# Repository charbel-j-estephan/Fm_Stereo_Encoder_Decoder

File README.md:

# FM Stereo Encoder and Decoder

An FM stereo transmission system that stays compatible with mono receivers. The encoder turns a left (G) and right (D) audio signal into one stereo multiplex (MPX) signal that drives an FM modulator. The decoder takes the received MPX and rebuilds G and D.

Communication Systems project, Notre Dame University Louaize.

## How it works

The encoder sends three things at once.

| Part                                 | Frequency       | Purpose                                       |
| ------------------------------------ | --------------- | --------------------------------------------- |
| G + D                                | 30 Hz to 15 kHz | What a mono receiver plays                    |
| 19 kHz pilot                         | 19 kHz          | Tells a stereo receiver to decode             |
| G − D on a suppressed 38 kHz carrier | 23 to 53 kHz    | The extra information a stereo receiver needs |

A mono receiver keeps only the band below 15 kHz, so it plays G + D. A stereo receiver locks to the pilot, doubles it to 38 kHz, recovers G − D and then rebuilds G and D.

## Repository layout

```
Encoder/              KiCad project and exports for the encoder board
Decoder/              KiCad project and exports for the decoder board
Simulation/LTspice/   LTspice encoder and decoder circuits with their models
Simulation/Simulink/  Simulink model of the full stereo FM system
Report/               IEEE format project report (encoder)
docs/img/             Images used in this README
  report/             Figures taken from the project report
  schematic/          Section views of the encoder schematic
```

### Encoder

| File                                            | What it is                         |
| ----------------------------------------------- | ---------------------------------- |
| `Encoder.kicad_pro`, `.kicad_sch`, `.kicad_pcb` | KiCad 10 project                   |
| `MC1496.kicad_sym`, `R0.kicad_sym`              | Symbol libraries the project needs |
| `Encoder_Schematic_color.pdf`                   | Full schematic in colour, A2 sheet |
| `Encoder_PCB_top_1to1_color.pdf`                | Top side of the board at 1:1 scale |
| `Encoder_3D_top.png`                            | 3D render of the board             |
| `FM_Encoder_Buy_List.xlsx`                      | Parts list with prices             |

Signal chain:

1. Input protection and AC coupling on both channels
2. TL072 buffers and Sallen Key low pass filters at 15 kHz
3. Sum (G + D) and difference (G − D) op amp matrix
4. CD4046 phase locked loop with a CD4013 divider, locked to an external 19 kHz reference, gives a 38 kHz carrier
5. MC1496 balanced modulator puts G − D on the 38 kHz carrier
6. MPX summer adds G + D, the modulated G − D and the pilot
7. NE5532 output low pass filters, then out on J4

#### Encoder schematic

The whole encoder fits on one A2 sheet. Each stage sits in its own framed section with a title and a one line note, and every stage output has a named test point.

Audio input and 15 kHz low pass filters. AC coupling, diode clamps to the ±9 V rails and a unity gain buffer on each channel, then two Sallen Key stages.

Sum and difference matrix. U6 makes G + D and U5 makes G − D.

38 kHz balanced modulator. The MC1496 puts G − D on the 38 kHz carrier, and U10A turns its differential output into one signal.

MPX summer and output filter. U8B adds G + D, the DSB signal and the 19 kHz pilot, U8A inverts it back, and three Sallen Key stages drive J4.

PLL. The CD4046 VCO runs at 38 kHz, and the CD4013 divides it by 2 so it locks to the 19 kHz pilot. JP1 picks the VCO or its inverted copy, then R54 and R55 set the carrier level.

Power input and decoupling. Reverse protection diodes, 22 µF bulk caps and a 100 nF pair on every op amp.

Test points, one header pin per stage output plus the ground pins.

Board facts:

- Runs from ±9 V on J1 and J2
- Audio in on J3 (pin 1 left, pin 2 right, pin 4 ground)
- 19 kHz reference in on J5
- MPX out on J4 (pin 1 signal, pin 4 ground)
- JP1 flips the carrier phase if left and right come out swapped
- About 149 by 150 mm, hand soldered, every IC in a socket, header pins as test points

| PCB layout                                                  | 3D view                                                            |
| ----------------------------------------------------------- | ------------------------------------------------------------------ |
|  |  |

| Fabricated PCB before assembly                                | Assembled board                                                       |
| ------------------------------------------------------------- | --------------------------------------------------------------------- |
|  |  |

### Decoder

| File                                            | What it is                         |
| ----------------------------------------------- | ---------------------------------- |
| `Decoder.kicad_pro`, `.kicad_sch`, `.kicad_pcb` | KiCad 10 project                   |
| `Decoder_Schematic_color.pdf`                   | Full schematic in colour           |
| `Decoder_PCB_top_1to1_color.pdf`                | Top side of the board at 1:1 scale |
| `Decoder_3D_top.png`                            | 3D render of the board             |

Signal chain:

1. NE5532 MPX input buffer
2. 15 kHz low pass cascade to recover G + D, which also feeds the mono output
3. CD4046 phase locked loop with a CD4013 divider regenerates the 38 kHz carrier from the 19 kHz reference
4. MC1496 demodulates G − D, followed by a second 15 kHz low pass cascade
5. RV1 and RV2 trim the levels, then a TL072 matrix forms G and D
6. A CD4052 switch selects stereo or mono, and TL072 stages drive the outputs

## Simulation

### LTspice

| File | What it is |
| --- | --- |
| `FM_Encoder.asc` | Full encoder circuit, 20 ms transient run |
| `FM_Decoder.asc` | Decoder circuit, fed by the recorded encoder output |
| `FM_Encoder_schematic.pdf` | Printed encoder schematic |
| `tl072.cir`, `NE5532.sub`, `mc1496.lib`, `CD4046.sub`, `CD4013.sub` | Part models |
| `*.asy` | Symbols for the parts above |
| `encoder_out.txt`, `carrier_38k.txt` | Encoder output and carrier recorded for the decoder run |

Keep every file in the same folder and open the `.asc` in LTspice. The encoder run takes about 15 minutes on a laptop. In the simulation the 19 kHz pilot comes from an op amp oscillator and the 38 kHz carrier from squaring the pilot in a second MC1496. The board replaced that part with an external 19 kHz reference and a CD4046 PLL.

With 1 kHz on G and 2 kHz on D, both at 0.2 V peak:

| Simulated matrix outputs | Simulated DSB SC output |
| --- | --- |
|  |  |

The simulated MPX spectrum holds G+D below 15 kHz, the pilot at 19 kHz and the G−D sidebands at 36, 37, 39 and 40 kHz. The 38 kHz carrier sits about 50 dB below the sidebands.

### Simulink

`FM_Stereo_System.slx` models the whole chain as a cross check: the encoder with 200 Hz and 500 Hz tones, an FM modulator and demodulator at 1 MHz with 75 kHz deviation, and a filter based decoder. Run `run_simulink_figures.m` from MATLAB to simulate it and export the model picture and the MPX signal. It sets `Ts = 3e-7` for you and does not change the model.

## Test results (encoder)

Measured on the assembled board in the lab.

| Check                              | Target        | Measured          |
| ---------------------------------- | ------------- | ----------------- |
| Supply rails                       | ±8.8 V        | +8.78 V / −8.80 V |
| Sum with both inputs joined        | 1.82 Vpp      | 1.80 Vpp          |
| Difference with both inputs joined | under 50 mVpp | 49.7 / 0 mVpp     |
| VCO locked to 19 kHz               | 38 kHz        | 38 kHz            |
| VCO tracking at 18.5 / 19.5 kHz    | 37 / 39 kHz   | 37 / 39 kHz       |
| DSB output, left only              | 3.5 to 8 Vpp  | 4.36 Vpp          |
| Mono audio at output               | 1.82 Vpp      | 1.90 Vpp          |
| Full MPX, left only plus pilot     | 2.5 to 5 Vpp  | 2.88 Vpp          |

Measured MPX output with 1 kHz on G and 2 kHz on D on the HMO722, with a 50 kHz span centred on 22.33 kHz. The upper trace is the time domain signal. The FFT below shows the two audio tones, the 19 kHz pilot and the lower sidebands of G − D near 36 and 37 kHz.

The full table and the spectrum analysis are in `Report/FM_Stereo_Encoder_Report.docx`.

## Opening the projects

Use KiCad 10. Open `Encoder/Encoder.kicad_pro` or `Decoder/Decoder.kicad_pro`. Keep the `.kicad_sym` files next to the encoder project.

## Team

- [charbel-j-estephan](https://charbel-j-estephan.com)
- Anthony El Chakar
- Alfred Sfeir
- Elie Dahdouh

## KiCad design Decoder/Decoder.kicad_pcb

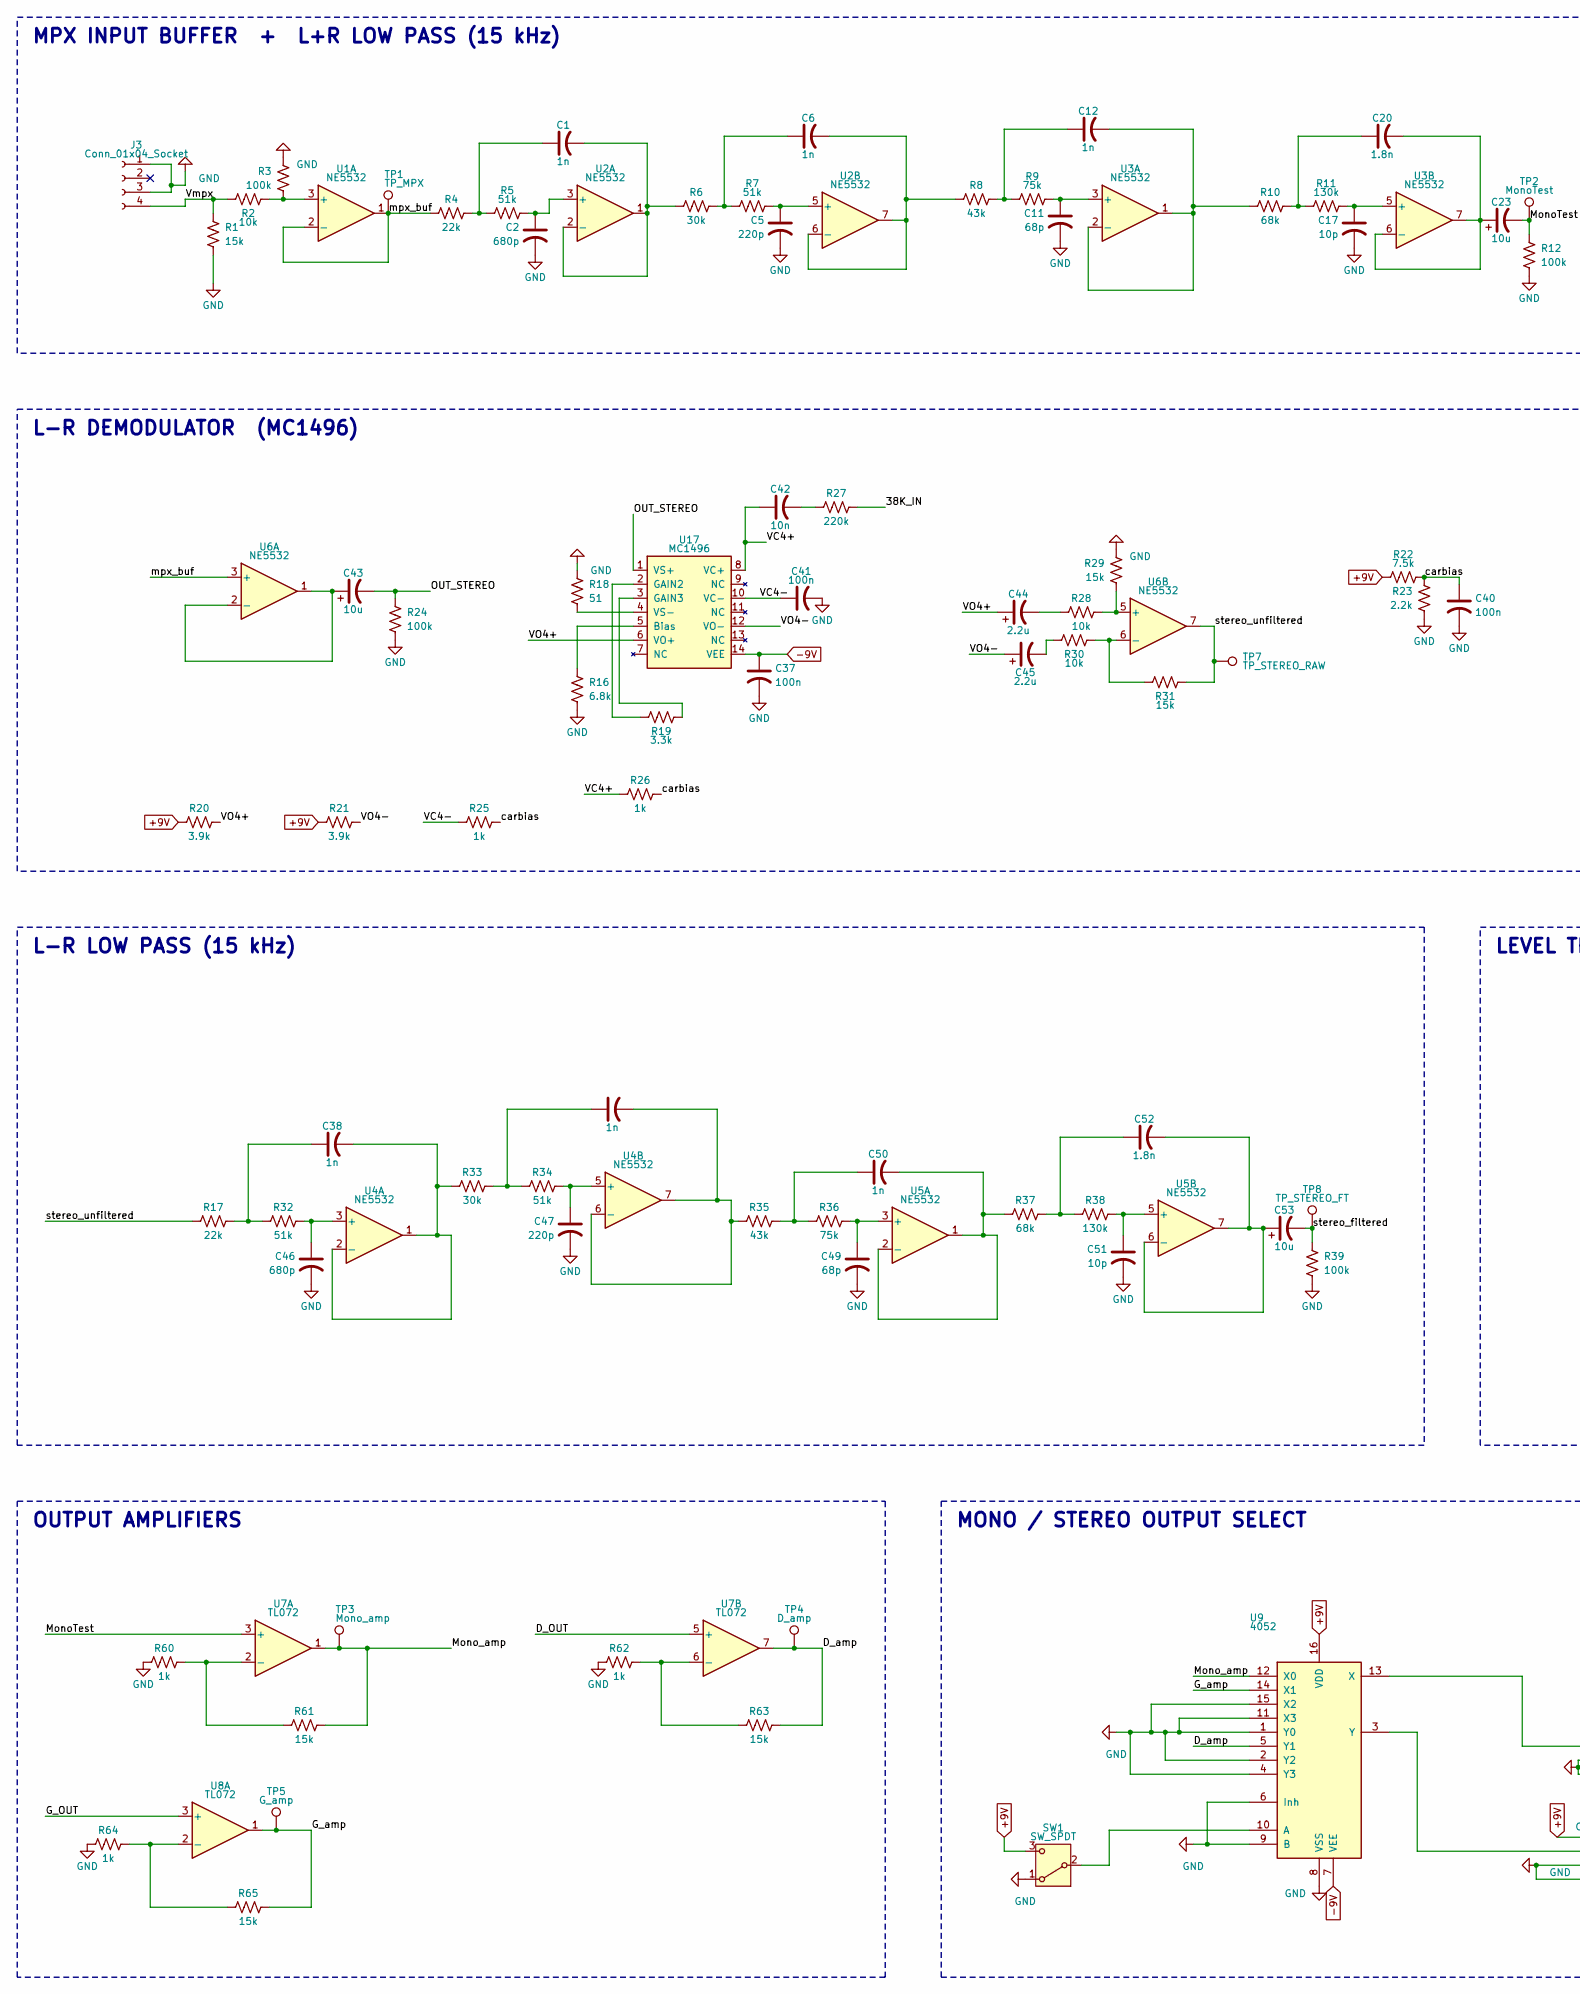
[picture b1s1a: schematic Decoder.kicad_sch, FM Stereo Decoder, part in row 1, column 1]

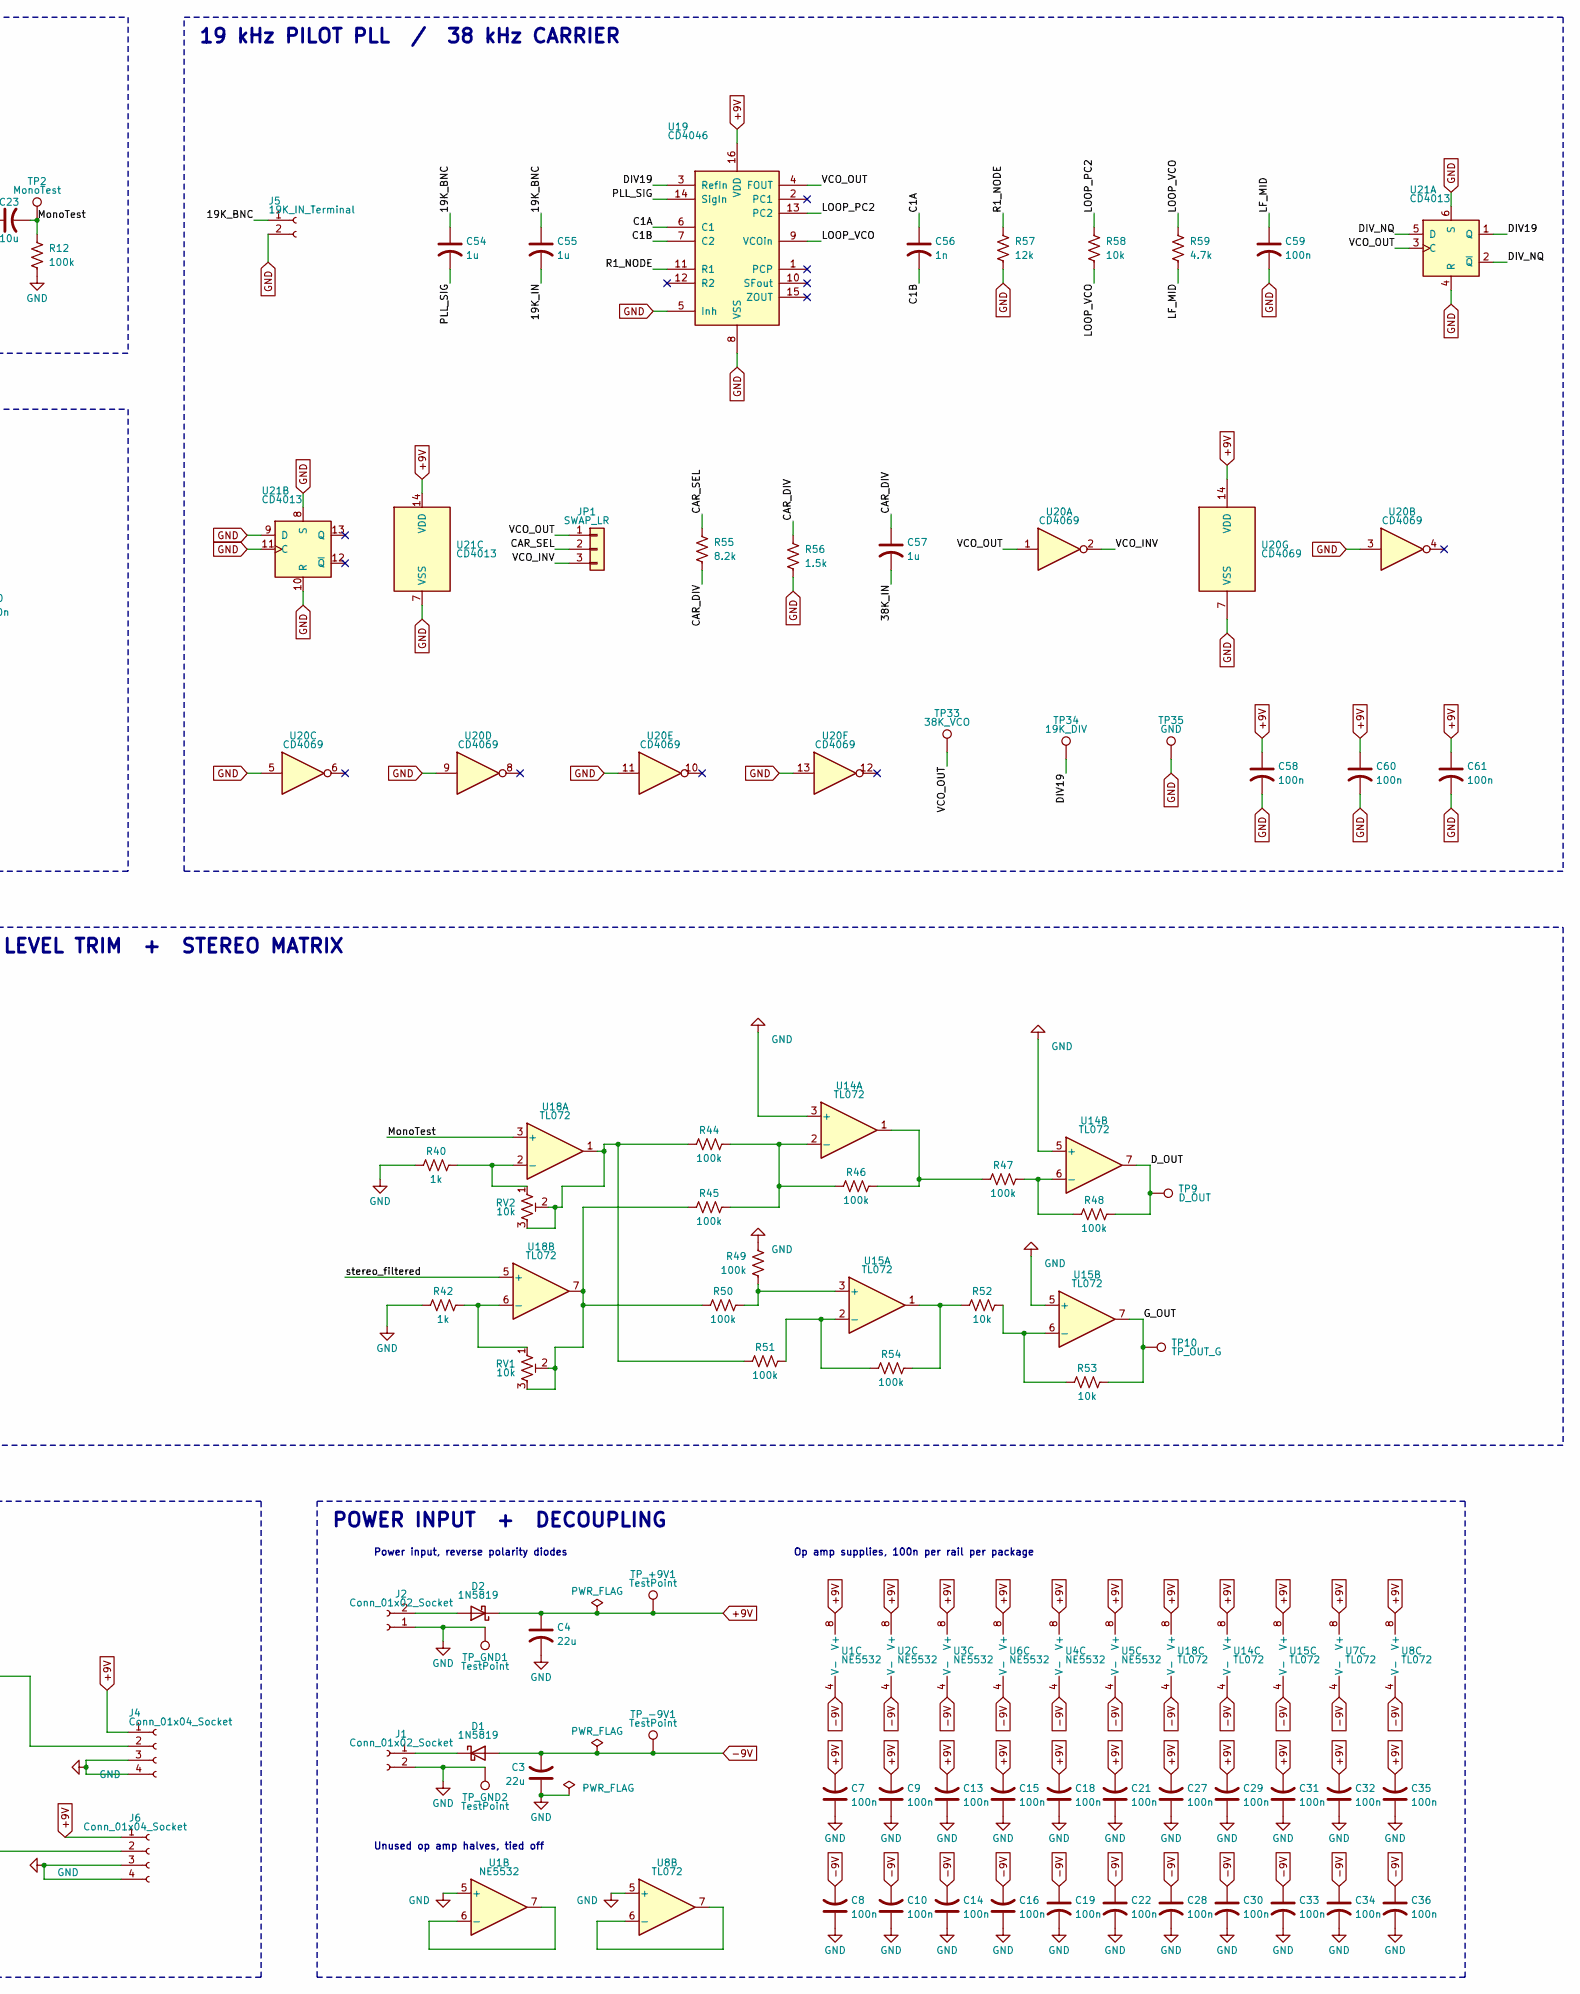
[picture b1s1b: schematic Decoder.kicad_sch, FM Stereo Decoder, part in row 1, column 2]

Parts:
C1, C6, C12, C38, C48, C50, C56: 1n; C_Disc_D5.0mm_W2.5mm_P5.00mm
C2, C46: 680p; C_Disc_D5.0mm_W2.5mm_P5.00mm
C3, C4: 22u; CP_Radial_D8.0mm_P3.50mm
C5, C47: 220p; C_Disc_D5.0mm_W2.5mm_P5.00mm
C7, C8, C9, C10, C13, C14, C15, C16, C18, C19, C21, C22, C27, C28, C29, C30, C31, C32, C33, C34, C35, C36, C37, C40, C41, C58, C59, C60, C61: 100n; C_Disc_D5.0mm_W2.5mm_P5.00mm
C11, C49: 68p; C_Disc_D5.0mm_W2.5mm_P5.00mm
C17, C51: 10p; C_Disc_D5.0mm_W2.5mm_P5.00mm
C20, C52: 1.8n; C_Disc_D5.0mm_W2.5mm_P5.00mm
C23, C43, C53: 10u; CP_Radial_D6.3mm_P2.50mm
C42: 10n; C_Disc_D5.0mm_W2.5mm_P5.00mm
C44, C45: 2.2u; CP_Radial_D6.3mm_P2.50mm
C54, C55, C57: 1u; C_Rect_L7.2mm_W3.5mm_P5.00mm
D1, D2: 1N5819; D_DO-41_SOD81_P10.16mm_Horizontal
J1, J2: Conn_01x02_Socket; TerminalBlock_Phoenix_MKDS-1,5-2-5.08_1x02_P5.08mm_Horizont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
J3: Conn_01x04_Socket; PinHeader_1x04_P2.54mm_Vertical
J4, J6: Conn_01x04_Socket; PinSocket_1x04_P2.54mm_Vertical
J5: 19K_IN_Terminal; TerminalBlock_Phoenix_MKDS-1,5-2-5.08_1x02_P5.08mm_Horizont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
JP1: SWAP_LR; PinHeader_1x03_P2.54mm_Vertical
R1, R29, R31, R61, R63, R65: 15k; R_Axial_DIN0207_L6.3mm_D2.5mm_P10.16mm_Horizontal
R2, R28, R30, R52, R53, R58: 10k; R_Axial_DIN0207_L6.3mm_D2.5mm_P10.16mm_Horizontal
R3, R12, R24, R39, R44, R45, R46, R47, R48, R49, R50, R51, R54: 100k; R_Axial_DIN0207_L6.3mm_D2.5mm_P10.16mm_Horizontal
R4, R17: 22k; R_Axial_DIN0207_L6.3mm_D2.5mm_P10.16mm_Horizontal
R5, R7, R32, R34: 51k; R_Axial_DIN0207_L6.3mm_D2.5mm_P10.16mm_Horizontal
R6, R33: 30k; R_Axial_DIN0207_L6.3mm_D2.5mm_P10.16mm_Horizontal
R8, R35: 43k; R_Axial_DIN0207_L6.3mm_D2.5mm_P10.16mm_Horizontal
R9, R36: 75k; R_Axial_DIN0207_L6.3mm_D2.5mm_P10.16mm_Horizontal
R10, R37: 68k; R_Axial_DIN0207_L6.3mm_D2.5mm_P10.16mm_Horizontal
R11, R38: 130k; R_Axial_DIN0207_L6.3mm_D2.5mm_P10.16mm_Horizontal
R16: 6.8k; R_Axial_DIN0207_L6.3mm_D2.5mm_P10.16mm_Horizontal
R18: 51; R_Axial_DIN0207_L6.3mm_D2.5mm_P10.16mm_Horizontal
R19: 3.3k; R_Axial_DIN0207_L6.3mm_D2.5mm_P10.16mm_Horizontal
R20, R21: 3.9k; R_Axial_DIN0207_L6.3mm_D2.5mm_P10.16mm_Horizontal
R22: 7.5k; R_Axial_DIN0207_L6.3mm_D2.5mm_P10.16mm_Horizontal
R23: 2.2k; R_Axial_DIN0207_L6.3mm_D2.5mm_P10.16mm_Horizontal
R25, R26, R40, R42, R60, R62, R64: 1k; R_Axial_DIN0207_L6.3mm_D2.5mm_P10.16mm_Horizontal
R27: 220k; R_Axial_DIN0207_L6.3mm_D2.5mm_P10.16mm_Horizontal
R55: 8.2k; R_Axial_DIN0207_L6.3mm_D2.5mm_P10.16mm_Horizontal
R56: 1.5k; R_Axial_DIN0207_L6.3mm_D2.5mm_P10.16mm_Horizontal
R57: 12k; R_Axial_DIN0207_L6.3mm_D2.5mm_P10.16mm_Horizontal
R59: 4.7k; R_Axial_DIN0207_L6.3mm_D2.5mm_P10.16mm_Horizontal
RV1, RV2: 10k; Potentiometer_Bourns_3296W_Vertical
SW1: SW_SPDT; PinHeader_1x03_P2.54mm_Vertical
TP1: TP_MPX; PinHeader_1x01_P2.54mm_Vertical
TP2: MonoTest; PinHeader_1x01_P2.54mm_Vertical
TP3: Mono_amp; PinHeader_1x01_P2.54mm_Vertical
TP4: D_amp; PinHeader_1x01_P2.54mm_Vertical
TP5: G_amp; PinHeader_1x01_P2.54mm_Vertical
TP7: TP_STEREO_RAW; PinHeader_1x01_P2.54mm_Vertical
TP8: TP_STEREO_FT; PinHeader_1x01_P2.54mm_Vertical
TP9: D_OUT; PinHeader_1x01_P2.54mm_Vertical
TP10: TP_OUT_G; PinHeader_1x01_P2.54mm_Vertical
TP33: 38K_VCO; PinHeader_1x01_P2.54mm_Vertical
TP34: 19K_DIV; PinHeader_1x01_P2.54mm_Vertical
TP35: GND; PinHeader_1x01_P2.54mm_Vertical
TP_+9V1: TestPoint; PinHeader_1x01_P2.54mm_Vertical
TP_-9V1: TestPoint; PinHeader_1x01_P2.54mm_Vertical
TP_GND1, TP_GND2: TestPoint; PinHeader_1x01_P2.54mm_Vertical
U1, U2, U3, U4, U5, U6: NE5532; DIP-8_W7.62mm_Socket
U7, U8, U14, U15, U18: TL072; DIP-8_W7.62mm_Socket
U9: 4052; DIP-16_W7.62mm_Socket
U17: MC1496; DIP-14_W7.62mm_Socket
U19: CD4046; DIP-16_W7.62mm_Socket
U20: CD4069; DIP-14_W7.62mm_Socket
U21: CD4013; DIP-14_W7.62mm_Socket

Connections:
+9V: C4.1, C7.2, C9.2, C13.2, C15.2, C18.2, C21.2, C27.2, C29.2, C31.2, C32.2, C35.2, C58.1, C60.1, C61.1, D2.1 (K), J4.1, J6.1, R20.2, R21.2, R22.2, SW1.3 (C), TP_+9V1.1 (1_1), U1.8 (V+), U2.8 (V+), U3.8 (V+), U4.8 (V+), U5.8 (V+), U6.8 (V+), U7.8 (V+), U8.8 (V+), U9.16 (VDD), U14.8 (V+), U15.8 (V+), U18.8 (V+), U19.16 (VDD), U20.14 (VDD), U21.14 (VDD)
-9V: C3.2, C8.2, C10.2, C14.2, C16.2, C19.1, C22.1, C28.1, C30.1, C33.1, C34.1, C36.1, C37.1, D1.2 (A), TP_-9V1.1 (1_1), U1.4 (V-), U2.4 (V-), U3.4 (V-), U4.4 (V-), U5.4 (V-), U6.4 (V-), U7.4 (V-), U8.4 (V-), U9.7 (VEE), U14.4 (V-), U15.4 (V-), U17.14 (VEE), U18.4 (V-)
/19K_BNC: C54.1, C55.1, J5.1
/19K_IN: C55.2
/38K_IN: C57.2, R27.1
/C1A: C56.1, U19.6 (C1)
/C1B: C56.2, U19.7 (C2)
/CAR_DIV: C57.1, R55.2, R56.1
/CAR_SEL: JP1.2, R55.1
/DIV19: TP34.1 (1_1), U19.3 (RefIn), U21.1 (Q)
/DIV_NQ: U21.2 (~Q), U21.5 (D)
/D_OUT: R48.1, TP9.1 (1_1), U7.5 (+), U14.7
/D_amp: R63.1, TP4.1 (1_1), U7.7, U9.5 (Y1)
/G_OUT: R53.1, TP10.1 (1_1), U8.3 (+), U15.7
/G_amp: R65.1, TP5.1 (1_1), U8.1, U9.14 (X1)
/LF_MID: C59.1, R59.2
/LOOP_PC2: R58.1, U19.13 (PC2)
/LOOP_VCO: R58.2, R59.1, U19.9 (VCOin)
/MonoTest: C23.2, R12.2, TP2.1 (1_1), U7.3 (+), U18.3 (+)
/Mono_amp: R61.1, TP3.1 (1_1), U7.1, U9.12 (X0)
/OUT_STEREO: C43.2, R24.2, U17.1 (VS+)
/PLL_SIG: C54.2, U19.14 (SigIn)
/R1_NODE: R57.1, U19.11 (R1)
/VC4+: C42.1, R26.2, U17.8 (VC+)
/VC4-: C41.1, R25.2, U17.10 (VC-)
/VCO_INV: JP1.3, U20.2
/VCO_OUT: JP1.1, TP33.1 (1_1), U19.4 (FOUT), U20.1, U21.3 (C)
/VO4+: C44.1, R20.1, U17.6 (VO+)
/VO4-: C45.1, R21.1, U17.12 (VO-)
/Vmpx: J3.4, R1.1, R2.1
/carbias: C40.1, R22.1, R23.1, R25.1, R26.1
/mpx_buf: R4.1, TP1.1 (1_1), U1.1, U1.2 (-), U6.3 (+)
/stereo_filtered: C53.2, R39.2, TP8.1 (1_1), U18.5 (+)
/stereo_unfiltered: R17.1, R31.1, TP7.1 (1_1), U6.7
GND: C2.2, C3.1, C4.2, C5.2, C7.1, C8.1, C9.1, C10.1, C11.2, C13.1, C14.1, C15.1, C16.1, C17.2, C18.1, C19.2, C21.1, C22.2, C27.1, C28.2, C29.1, C30.2, C31.1, C32.1, C33.2, C34.2, C35.1, C36.2, C37.2, C40.2, C41.2, C46.2, C47.2, C49.2, C51.2, C58.2, C59.2, C60.2, C61.2, J1.2, J2.1, J3.1, J3.3, J4.3, J4.4, J5.2, J6.3, J6.4, R1.2, R3.1, R12.1, R16.1, R18.1, R23.2, R24.1, R29.1, R39.1, R40.2, R42.2, R49.1, R56.2, R57.2, R60.2, R62.2, R64.2, SW1.1 (A), TP35.1 (1_1), TP_GND1.1 (1_1), TP_GND2.1 (1_1), U1.5 (+), U8.5 (+), U9.1 (Y0), U9.2 (Y2), U9.4 (Y3), U9.6 (Inh), U9.8 (VSS), U9.9 (B), U9.11 (X3), U9.15 (X2), U14.3 (+), U14.5 (+), U15.5 (+), U19.5 (Inh), U19.8 (VSS), U20.3, U20.5, U20.7 (VSS), U20.9, U20.11, U20.13, U21.4 (R), U21.6 (S), U21.7 (VSS), U21.8 (S), U21.9 (D), U21.10 (R), U21.11 (C)
unnamed: C1.1, R4.2, R5.1
unnamed: C6.1, R6.2, R7.1
unnamed: C12.1, R8.2, R9.1
unnamed: C20.1, R10.2, R11.1
unnamed: C38.1, R17.2, R32.1
unnamed: C42.2, R27.2
unnamed: C44.2, R28.2
unnamed: C45.2, R30.2
unnamed: C48.1, R33.2, R34.1
unnamed: C50.1, R35.2, R36.1
unnamed: C52.1, R37.2, R38.1
unnamed: D1.1 (K), J1.1
unnamed: D2.2 (A), J2.2
unnamed: J4.2, U9.13 (X)
unnamed: J6.2, U9.3 (Y)
unnamed: R44.2, R51.2, RV2.2, RV2.3, U18.1
unnamed: R45.2, R50.2, RV1.2, RV1.3, U18.7
unnamed: R46.1, R47.2, U14.1
unnamed: R52.2, R54.1, U15.1
unnamed: SW1.2 (B), U9.10 (A)
unnamed: R2.2, R3.2, U1.3 (+)
unnamed: U1.6 (-), U1.7
unnamed: C2.1, R5.2, U2.3 (+)
unnamed: C1.2, R6.1, U2.1, U2.2 (-)
unnamed: C5.1, R7.2, U2.5 (+)
unnamed: C6.2, R8.1, U2.6 (-), U2.7
unnamed: C11.1, R9.2, U3.3 (+)
unnamed: C12.2, R10.1, U3.1, U3.2 (-)
unnamed: C17.1, R11.2, U3.5 (+)
unnamed: C20.2, C23.1, U3.6 (-), U3.7
unnamed: C46.1, R32.2, U4.3 (+)
unnamed: C38.2, R33.1, U4.1, U4.2 (-)
unnamed: C47.1, R34.2, U4.5 (+)
unnamed: C48.2, R35.1, U4.6 (-), U4.7
unnamed: C49.1, R36.2, U5.3 (+)
unnamed: C50.2, R37.1, U5.1, U5.2 (-)
unnamed: C51.1, R38.2, U5.5 (+)
unnamed: C52.2, C53.1, U5.6 (-), U5.7
unnamed: C43.1, U6.1, U6.2 (-)
unnamed: R28.1, R29.2, U6.5 (+)
unnamed: R30.1, R31.2, U6.6 (-)
unnamed: R60.1, R61.2, U7.2 (-)
unnamed: R62.1, R63.2, U7.6 (-)
unnamed: R64.1, R65.2, U8.2 (-)
unnamed: U8.6 (-), U8.7
unnamed: R44.1, R45.1, R46.2, U14.2 (-)
unnamed: R47.1, R48.2, U14.6 (-)
unnamed: R49.2, R50.1, U15.3 (+)
unnamed: R51.1, R54.2, U15.2 (-)
unnamed: R52.1, R53.2, U15.6 (-)
unnamed: R16.2, U17.5 (Bias)
unnamed: R19.2, U17.2 (GAIN2)
unnamed: R19.1, U17.3 (GAIN3)
unnamed: R18.2, U17.4 (VS-)
unnamed: R40.1, RV2.1, U18.2 (-)
unnamed: R42.1, RV1.1, U18.6 (-)

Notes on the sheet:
LEVEL TRIM + STEREO MATRIX
MONO / STEREO OUTPUT SELECT
Power input, reverse polarity diodes
OUTPUT AMPLIFIERS
Op amp supplies, 100n per rail per package
MPX INPUT BUFFER + L+R LOW PASS (15 kHz)
Unused op amp halves, tied off
L-R LOW PASS (15 kHz)
L-R DEMODULATOR (MC1496)
19 kHz PILOT PLL / 38 kHz CARRIER
POWER INPUT + DECOUPLING

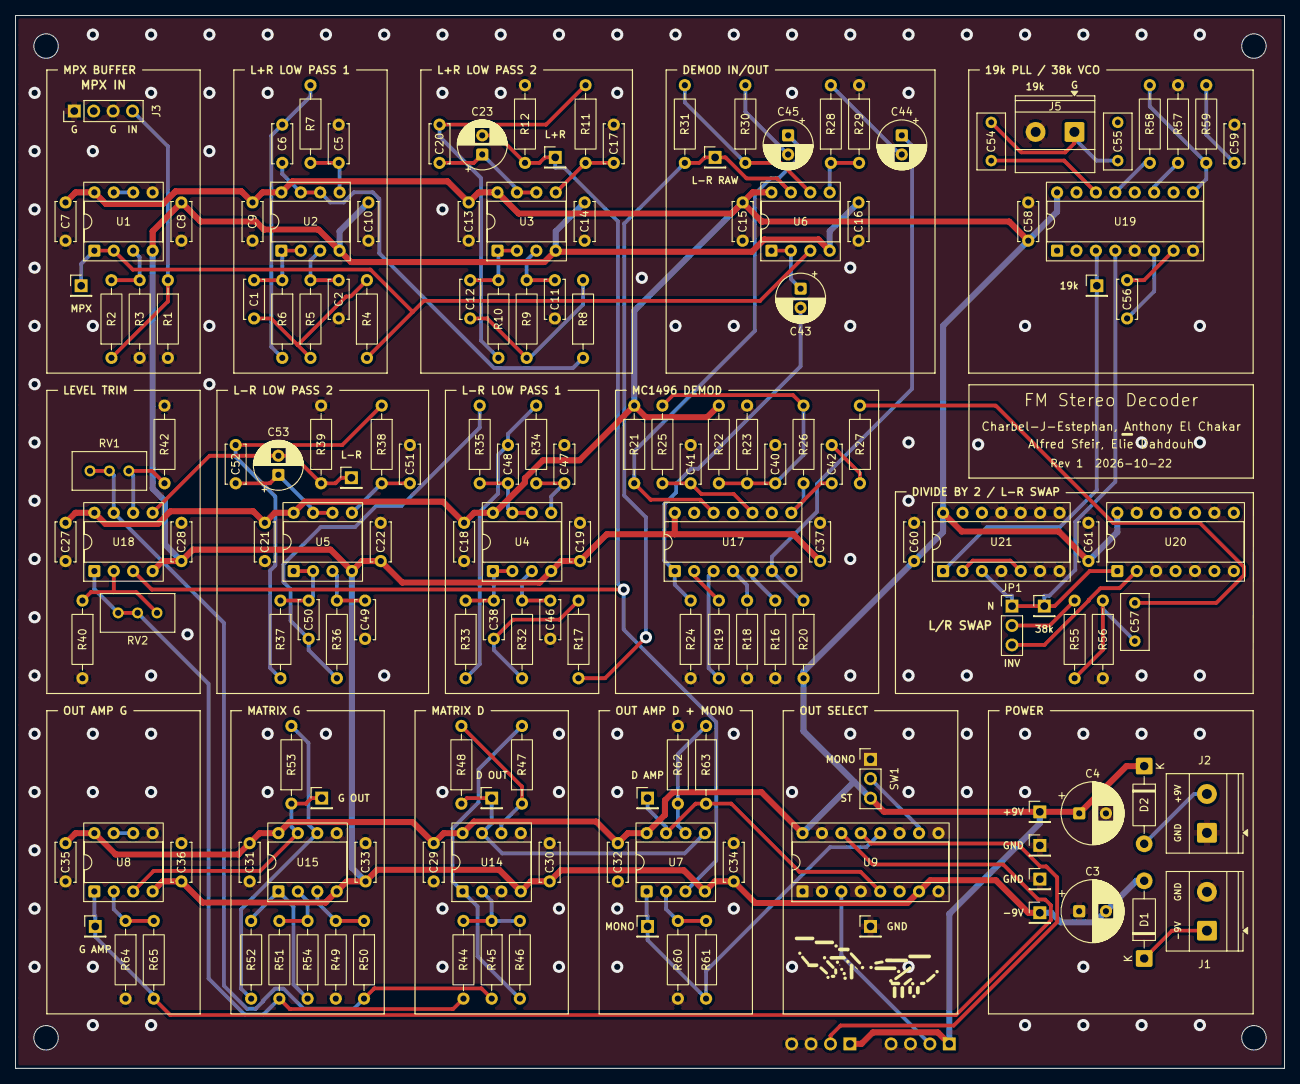
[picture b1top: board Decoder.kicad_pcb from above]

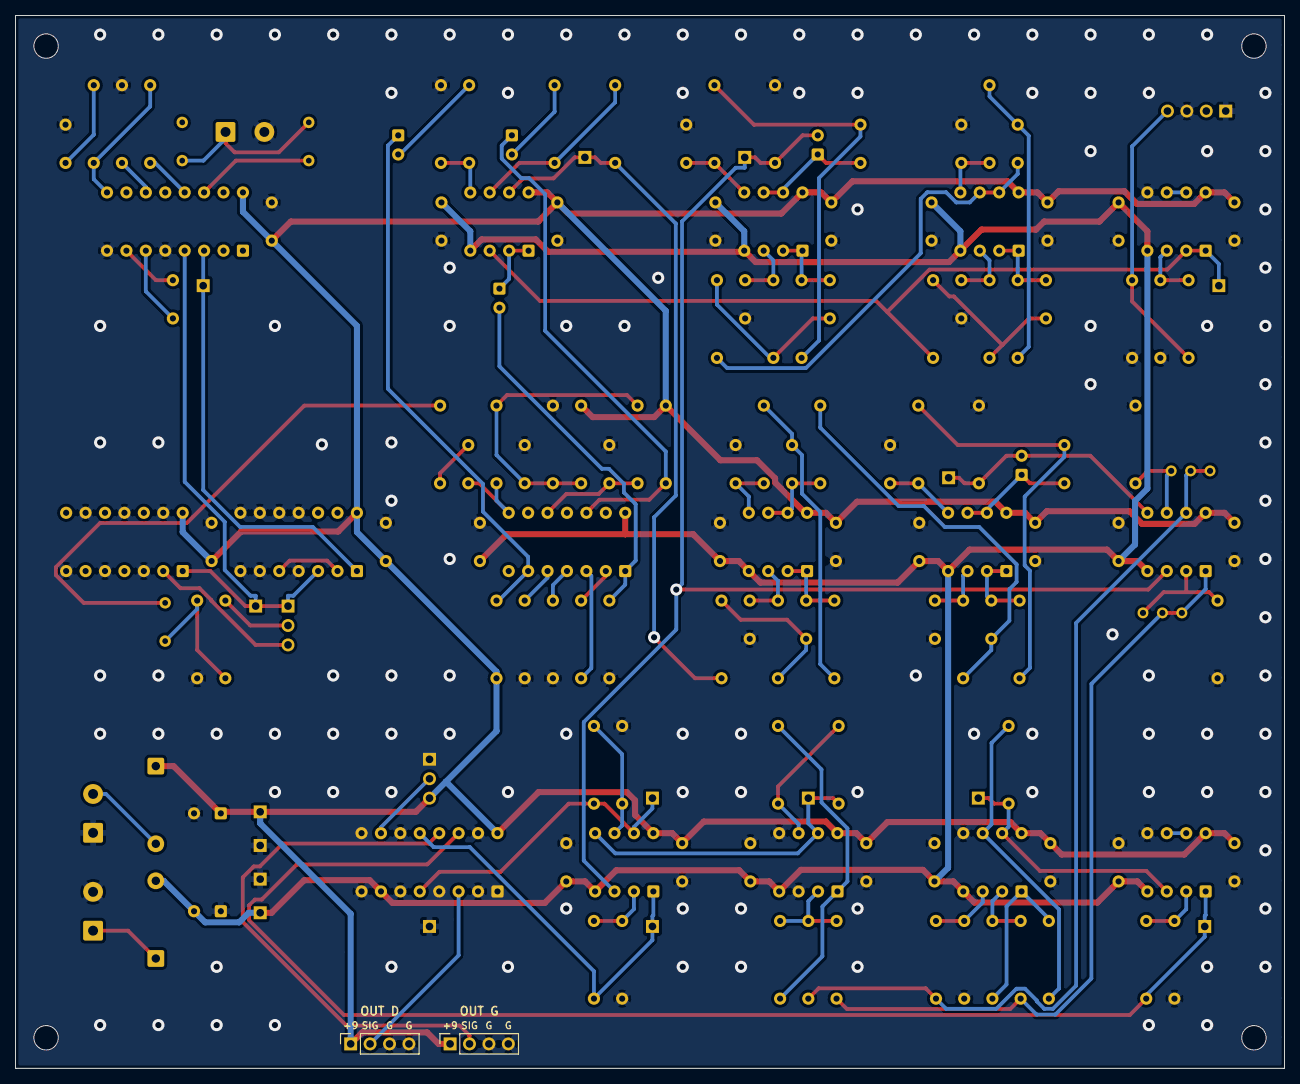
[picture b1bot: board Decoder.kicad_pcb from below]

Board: 2 copper layers, 166.0 x 137.7 mm, 161 parts (2 on the bottom side), 90 nets.
